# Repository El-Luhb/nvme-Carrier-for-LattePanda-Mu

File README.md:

# nvme Carrier for LattePanda Mu

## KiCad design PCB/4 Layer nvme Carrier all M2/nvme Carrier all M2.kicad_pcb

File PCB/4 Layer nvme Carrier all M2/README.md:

# nvme Carrier for LattePanda Mu

## Specification

### Power Input

- DC 5.5x2.5mm: 12V (Max 10A)
- USB-C 15V

### Internal Interfaces

- 1x M.2 M Key 2242 & 2280 (PCIe 3.0 x1) on the frontside
- 1x M.2 E Key 2242 (PCIe 3.0 x1) on the frontside
- 6x M.2 M Key up to 2280 (PCIe 3.0 x1) on the backside
- RTC battery socket (CR1220 3V)
- CPU fan socket
- 2x CASE fan socket (1x only when using 12V)
- 3x USB 2.0 (1x USB Port)
- MOLEX Connector for 5V (2A) and 12V Supply to HDDs (only when using 12V)

### External Interfaces

- 1x USB 3.2 10Gbps
- 2x USB 2.0
- HDMI 2.0

### Dimension

ITX, 170mm×170mm

### Extras

Carrier BIOS

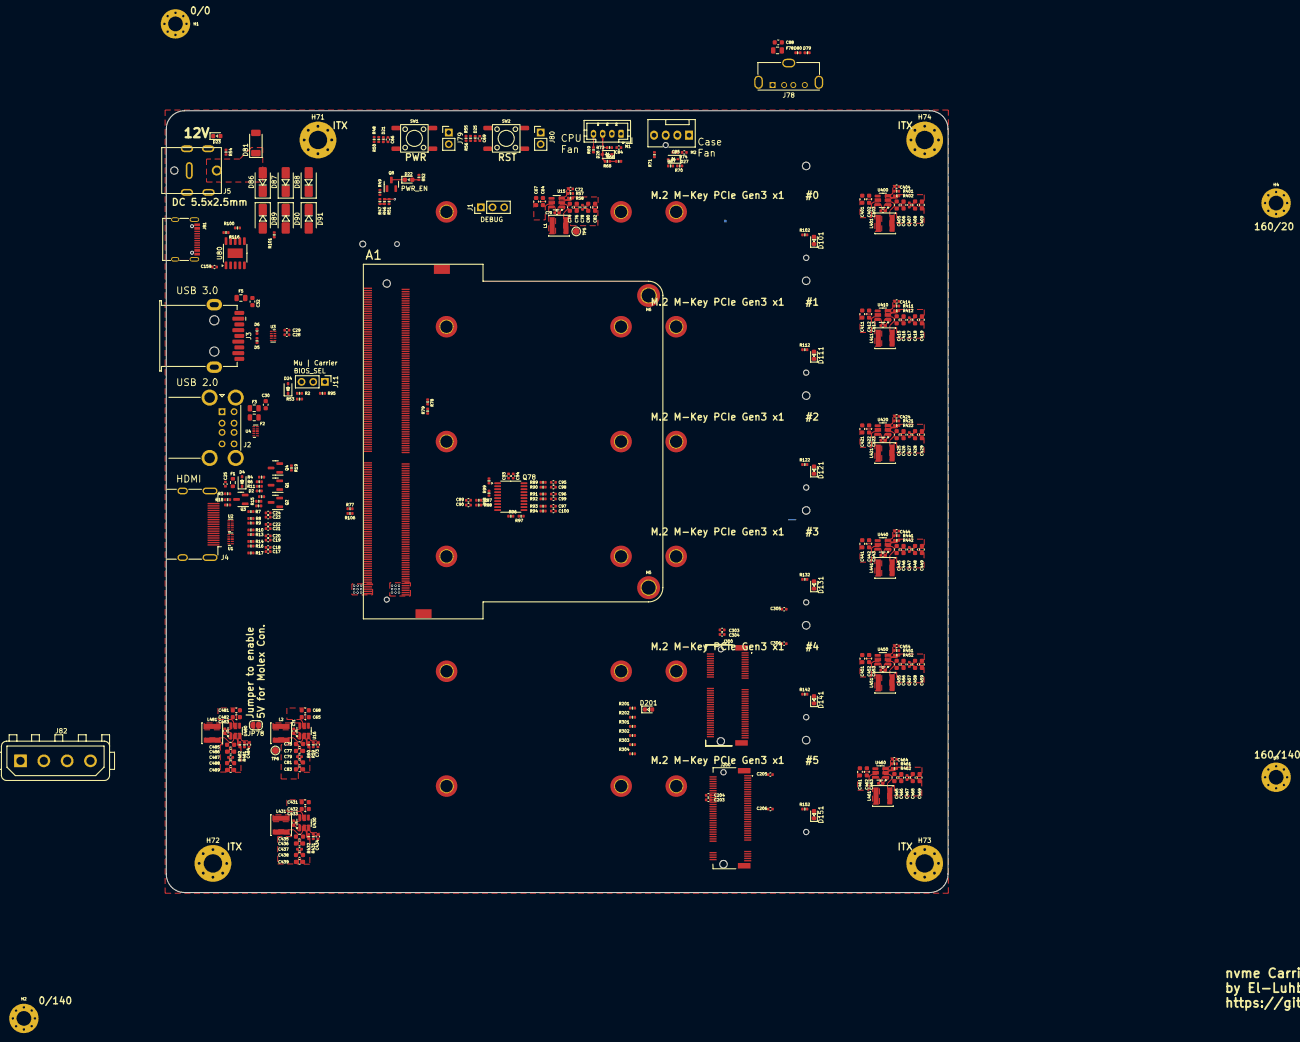
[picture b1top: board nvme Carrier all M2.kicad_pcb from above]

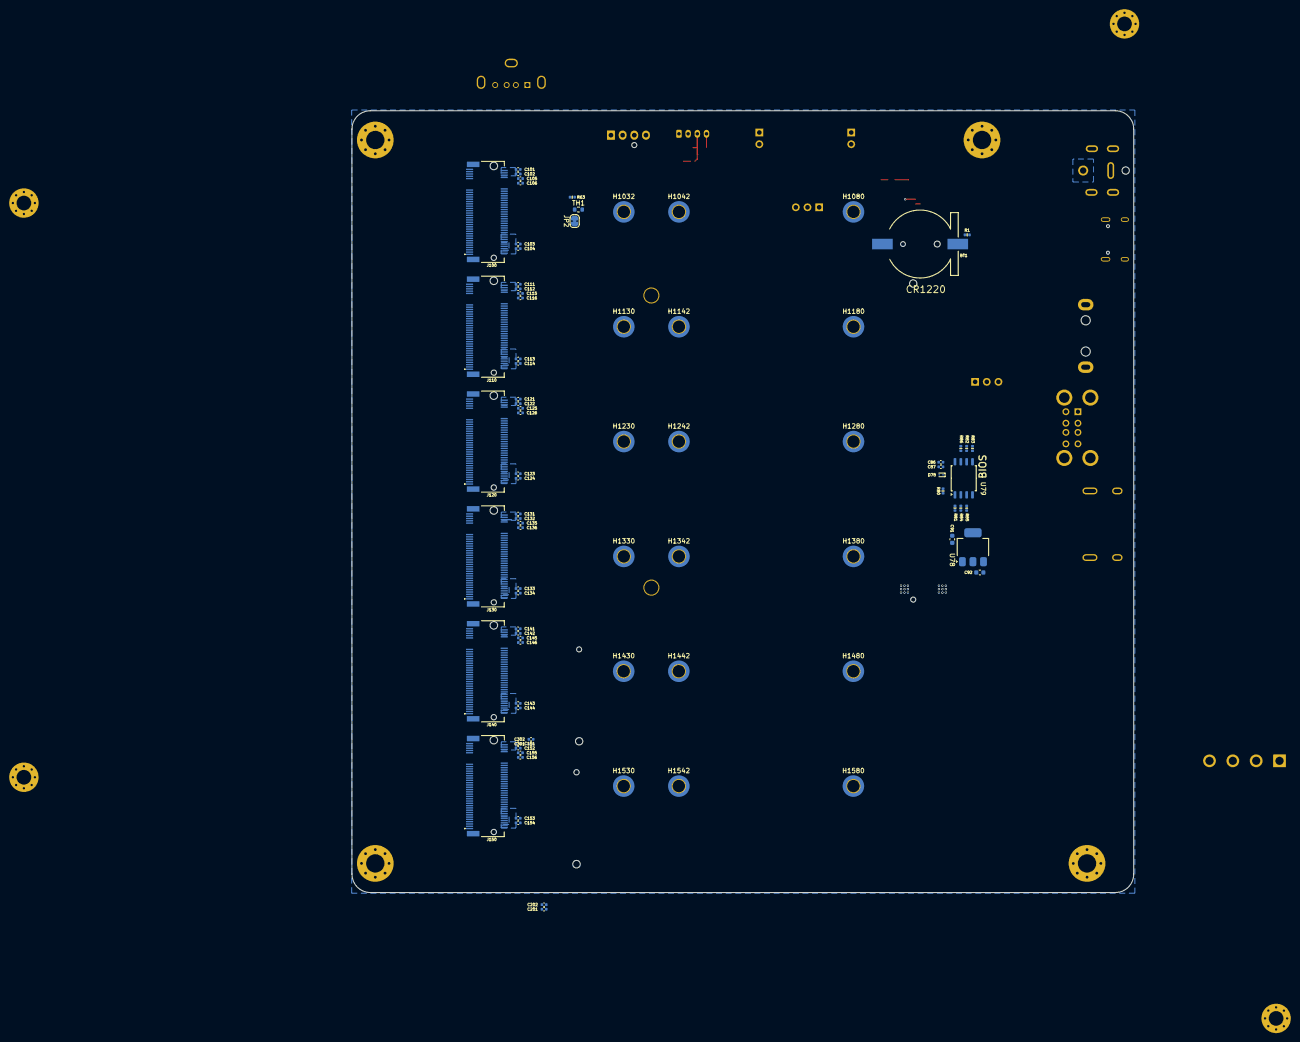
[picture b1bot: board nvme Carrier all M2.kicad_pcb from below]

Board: 4 copper layers, 170.2 x 170.2 mm, 394 parts (83 on the bottom side), 250 nets.

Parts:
A1: LattePanda_Mu; LattePanda_Module_H8.0mm_Horizontal
BT1: Battery_Cell; Battery_Holder_CR1220_S8411-45R
C17, C18, C19, C20, C21, C22, C23, C24, C25, C28, C29, C70, C71, C78, C79, C84, C85, C102, C104, C112, C114, C122, C124, C132, C134, C142, C144, C152, C154, C204, C206, C304, C306, C403, C407, C413, C417, C423, C427, C433, C437, C443, C447, C453, C457, C463, C467, C483, C487: 100nF/50V; C_0402_1005Metric
C30, C32, C74, C75, C76, C77, C80, C81, C82, C83, C88, C91, C405, C406, C408, C409, C415, C416, C418, C419, C425, C426, C428, C429, C435, C436, C438, C439, C445, C446, C448, C449, C455, C456, C458, C459, C465, C466, C468, C469, C485, C486, C488, C489: 22uF/10V; C_0603_1608Metric
C64, C65, C67, C68, C92, C401, C402, C411, C412, C421, C422, C431, C432, C441, C442, C451, C452, C461, C462, C481, C482: 22uF/16V; C_0603_1608Metric
C66, C69, C159: 1uF/16V; C_0402_1005Metric
C72, C73, C404, C414, C424, C434, C444, C454, C464, C484: 12pF/50V; C_0402_1005Metric
C86, C93: 22uF/6.3V; C_0402_1005Metric
C87, C89, C90, C94, C95, C96, C97, C98, C99, C100: 0.1uF/16V; C_0402_1005Metric
C101, C103, C111, C113, C121, C123, C131, C133, C141, C143, C151, C153, C203, C205, C303, C305: 10uF/10V; C_0402_1005Metric
C105, C106, C115, C116, C125, C126, C135, C136, C145, C146, C155, C156, C201, C202, C301, C302: 220nF/50V; C_0402_1005Metric
D1, D2, D3, D5, D6, D21, D25, D79, D80: ESD5V0B03; D_0402_1005Metric
D4, D26, D27: 1N5819WS; D_SOD-323
D22, D23, D101, D111, D121, D131, D141, D151, D201: LED_G; LED_0603_1608Metric
D24: 3V3 Izt=5mA; D_SOD-323
D78: D_Schottky; D_SOD-923
D81: PTVS12VP1UP; D_SOD-128
D86, D87, D88, D89, D90, D91: SS54; D_SMA
F1: 6V/50mA; R_0603_1608Metric
F2, F3, F78: 6V/1A; Fuse_0805_2012Metric
F5: 6V/2A; Fuse_0805_2012Metric
H1, H2, H3, H4: MountingHole_Pad; MountingHole_3.2mm_M3_Pad_Via
H5, H6: MountingHole_Pad; MountingHole_3mm_M2_Pad_TopOnly
H71, H72, H73, H74: MountingHole_Pad; MountingHole_4mm_Pad_Via
H1032, H1042, H1080, H1130, H1142, H1180, H1230, H1242, H1280, H1330, H1342, H1380, H1430, H1442, H1480, H1530, H1542, H1580: MountingHole_M2.5; MountingHole_2.7mm_M2.5_DIN965_Pad_TopBottom
J1, J11: Conn_01x03_Pin; PinHeader_1x03_P2.54mm_Vertical
J2: USB_A_Stacked; USB_A_CUI_UJ2-ADH-TH_Horizontal_Stacked
J3: USB3_A; USB3_A_Receptacle_Wuerth_692122030100
J4: HDMI_A; HDMI_A_Molex_208658-1001_Horizontal
J5: Barrel_Jack_Switch; DC_Jack_DC007B_30V_10A
J78: USB_A; USB_A_Molex_105057_Vertical
J79, J80: Conn_01x02_Pin; PinHeader_1x02_P2.54mm_Vertical
J81: USB_C_Receptacle_USB2.0_14P; USB_C_Receptacle_G-Switch_GT-USB-7010ASV
J82: Conn_01x04; TE_MATE-N-LOK_350211-1_1x04_P5.08mm_Vertical
J100, J110, J120, J130, J140, J150, J200: Bus_M.2_Socket_M; PCIe_M.2_Connectors_P=0.5mm_H=4.2mm_KeyM
J300: Bus_M.2_Socket_E; PCIe_M.2_Connectors_P=0.5mm_H=4.2mm_KeyE
JP2: NTC_Test; SolderJumper-2_P1.3mm_Bridged_RoundedPad1.0x1.5mm
JP78: SolderJumper_2_Open; SolderJumper-2_P1.3mm_Open_RoundedPad1.0x1.5mm
L1, L2, L401, L411, L421, L431, L441, L451, L461, L481: 2.2uH/4.3A; L_Sunlord_SWPA4020S
M1: Fan_4pin; JST_PH_B4B-PH-K_1x04_P2.00mm_Vertical
M2: Fan_4pin; FanPinHeader_1x04_P2.54mm_Vertical
Q1, Q8: 2N7002; SOT-23
Q2, Q3, Q4: 2SK3018; SOT-23
Q78: 9DBL411BGLFT; TSSOP-20_4.4x6.5mm_P0.65mm
R1, R11, R47, R101: 1K/1%; R_0402_1005Metric
R2, R49, R50, R56, R58, R63, R95, R100, R303, R304, R482: 10K/1%; R_0402_1005Metric
R3, R5, R15, R18, R19, R52, R53, R102, R112, R122, R132, R142, R152, R201: 2.2K/1%; R_0402_1005Metric
R4: 1M/1%; R_0402_1005Metric
R6, R54, R66, R67, R68, R70: 21.5K/1%; R_0402_1005Metric
R7, R8, R9, R10, R13, R14, R16, R17: 470R/1%; R_0402_1005Metric
R46, R48, R55, R69, R71: 100R/1%; R_0402_1005Metric
R51, R59, R77, R78, R79, R96, R97, R98, R99, R106, R401, R411, R421, R431, R441, R451, R461: 100K/1%; R_0402_1005Metric
R57, R481: 75K/1%; R_0402_1005Metric
R60, R402, R412, R422, R432, R442, R452, R462: 22K/1%; R_0402_1005Metric
R72, R74: 4.7K/1%; R_0402_1005Metric
R80: 120K/1%; R_0402_1005Metric
R81: 0R; R_0402_1005Metric
R82, R83, R84, R85, R86: 15R/1%; R_0402_1005Metric
R87, R88, R89, R90, R91, R92, R93, R94: 33R/5%; R_0402_1005Metric
R116: 56K/1%; R_0402_1005Metric
R202, R301, R302: 0R/1%; R_0402_1005Metric
SW1, SW2: SW_Push; SW_Push_6x6x6
TH1: NTC-10K; R_0603_1608Metric
TP5, TP6: TestPoint; TestPoint_Pad_D1.5mm
U1, U2: TPAZ1023-04F; Diodes_UDFN-10_1.0x2.5mm_P0.5mm
U3, U4: ULC0524P; Diodes_UDFN-10_1.0x2.5mm_P0.5mm
U15, U16, U400, U410, U420, U430, U440, U450, U460, U480: SY8253ADC; TSOT-23-6
U78: AMS1117-3.3; SOT-223-3_TabPin2
U79: W25Q128JVSIQ; SOIC-8_5.23x5.23mm_P1.27mm
U80: CH224K; SSOP-10-1EP_3.9x4.9mm_P1mm_EP2.1x3.3mm

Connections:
5V_HDMI_VCC: C25.1, D4.1 (K), F1.1, R15.1, R18.1
+3V3: C73.1, C75.2, C77.2, C79.1, C81.2, C83.2, C93.1, C94.1, C203.2, C204.2, C205.2, C206.2, C303.2, C304.2, C305.2, C306.2, J200.2 (3.3V), J200.4 (3.3V), J200.12 (3.3V), J200.14 (3.3V), J200.16 (3.3V), J200.18 (3.3V), J200.70 (3.3V), J200.72 (3.3V), J200.74 (3.3V), J300.2 (3.3V), J300.4 (3.3V), J300.72 (3.3V), J300.74 (3.3V), L2.2, Q1.1 (G), Q2.1 (G), Q3.1 (G), Q78.4 (VDDA), Q78.9 (VDD_IO), Q78.18 (VDD_IO), R3.1, R4.1, R5.1, R50.2, R52.2, R56.2, R59.2, R63.1, R201.2, R303.2, R304.1, TP6.1
+3V3 Bios: C91.2, D78.2 (A), U78.2 (VO)
+3V3a: C101.2, C102.2, C103.2, C104.2, C404.1, C405.2, C406.2, C407.1, C408.2, C409.2, J100.2 (3.3V), J100.4 (3.3V), J100.12 (3.3V), J100.14 (3.3V), J100.16 (3.3V), J100.18 (3.3V), J100.70 (3.3V), J100.72 (3.3V), J100.74 (3.3V), L401.2, R102.2, R401.2
+3V3b: C111.2, C112.2, C113.2, C114.2, C414.1, C415.2, C416.2, C417.1, C418.2, C419.2, J110.2 (3.3V), J110.4 (3.3V), J110.12 (3.3V), J110.14 (3.3V), J110.16 (3.3V), J110.18 (3.3V), J110.70 (3.3V), J110.72 (3.3V), J110.74 (3.3V), L411.2, R112.2, R411.2
+3V3c: C121.2, C122.2, C123.2, C124.2, C424.1, C425.2, C426.2, C427.1, C428.2, C429.2, J120.2 (3.3V), J120.4 (3.3V), J120.12 (3.3V), J120.14 (3.3V), J120.16 (3.3V), J120.18 (3.3V), J120.70 (3.3V), J120.72 (3.3V), J120.74 (3.3V), L421.2, R122.2, R421.2
+3V3d: C131.2, C132.2, C133.2, C134.2, C444.1, C445.2, C446.2, C447.1, C448.2, C449.2, J130.2 (3.3V), J130.4 (3.3V), J130.12 (3.3V), J130.14 (3.3V), J130.16 (3.3V), J130.18 (3.3V), J130.70 (3.3V), J130.72 (3.3V), J130.74 (3.3V), L441.2, R132.2, R441.2
+3V3e: C141.2, C142.2, C143.2, C144.2, C454.1, C455.2, C456.2, C457.1, C458.2, C459.2, J140.2 (3.3V), J140.4 (3.3V), J140.12 (3.3V), J140.14 (3.3V), J140.16 (3.3V), J140.18 (3.3V), J140.70 (3.3V), J140.72 (3.3V), J140.74 (3.3V), L451.2, R142.2, R451.2
+3V3f: C151.2, C152.2, C153.2, C154.2, C464.1, C465.2, C466.2, C467.1, C468.2, C469.2, J150.2 (3.3V), J150.4 (3.3V), J150.12 (3.3V), J150.14 (3.3V), J150.16 (3.3V), J150.18 (3.3V), J150.70 (3.3V), J150.72 (3.3V), J150.74 (3.3V), L461.2, R152.2, R461.2
+3V3g: C434.1, C435.2, C436.2, C437.1, C438.2, C439.2, L431.2, R431.2
+5V: C30.2, C32.2, C72.1, C74.2, C76.2, C78.1, C80.2, C82.2, C84.1, C88.2, D4.2 (A), D26.1 (K), F2.1, F3.1, F5.1, F78.1, L1.2, M1.2 (+), R57.2, R72.1, TP5.1
+5Va: C484.1, C485.2, C486.2, C487.1, C488.2, C489.2, J82.4, L481.2, R481.2
+12V: A1.250 (VIN), A1.251 (VIN), A1.252 (VIN), A1.253 (VIN), A1.254 (VIN), A1.255 (VIN), A1.256 (VIN), A1.257 (VIN), A1.258 (VIN), A1.259 (VIN), A1.260 (VIN), C85.1, D27.1 (K), D81.1 (K), D86.2 (A), D87.2 (A), D88.2 (A), J5.1, J82.1, M2.2 (+), R74.1
+15V: D89.2 (A), D90.2 (A), D91.2 (A), J81.A4 (VBUS), J81.A9 (VBUS), J81.B4 (VBUS), J81.B9 (VBUS), R100.2, R101.2
+BATT: A1.115 (VBAT), R1.1
/BIOS/SPI-CS: A1.165 (~SPI_CS), R81.1
/BIOS/SPI-IO0: A1.159 (SPI_MOSI/SPI_IO0), R83.1
/BIOS/SPI-IO1: A1.163 (SPI_MISO/SPI_IO1), R84.1
/BIOS/SPI-IO2: A1.161 (SPI_IO2), R85.1
/BIOS/SPI-IO3: A1.153 (SPI_IO3), R86.1
/BIOS/SPI_CLK: A1.155 (SPI_CLK), R82.1
/Fan_Temp/FAN_1_PWM: A1.2 (FAN1_PWM), R69.1
/Fan_Temp/FAN_1_TAC: A1.4 (FAN1_TAC), R66.1, R68.2
/Fan_Temp/FAN_2_PWM: A1.6 (FAN2_PWM), R71.1
/Fan_Temp/FAN_2_TAC: A1.8 (FAN2_TAC), R67.1, R70.1
/Fan_Temp/TEMP: A1.9 (TSENSE), JP2.1 (A)
/HDMI DP/DDC_SCL: D1.2 (A2), J4.15 (SCL), Q2.3 (D), R15.2
/HDMI DP/DDC_SDA: D3.2 (A2), J4.16 (SDA), Q3.3 (D), R18.2
/HDMI DP/DDI_B_DDC_SCL: A1.171 (DDIB_DDC_SCL), Q2.2 (S), R5.2
/HDMI DP/DDI_B_DDC_SDA: A1.169 (DDIB_DDC_SDA), Q3.2 (S), R3.2
/HDMI DP/DDI_B_HPD: A1.183 (DDIB_HPD), Q1.2 (S), R4.2
/HDMI DP/DDI_B_TX0+: A1.217 (DDIB_TX0+), C17.1
/HDMI DP/DDI_B_TX0-: A1.215 (DDIB_TX0-), C18.1
/HDMI DP/DDI_B_TX1+: A1.211 (DDIB_TX1+), C19.1
/HDMI DP/DDI_B_TX1-: A1.209 (DDIB_TX1-), C20.1
/HDMI DP/DDI_B_TX2+: A1.205 (DDIB_TX2+), C21.1
/HDMI DP/DDI_B_TX2-: A1.203 (DDIB_TX2-), C22.1
/HDMI DP/DDI_B_TX3+: A1.199 (DDIB_TX3+), C23.1
/HDMI DP/DDI_B_TX3-: A1.197 (DDIB_TX3-), C24.1
/HDMI DP/HPD: D2.2 (A2), J4.19 (HPD), R11.2
/HDMI DP/TCP_0_HPD: A1.187 (TCP0_HPD), R106.1
/HDMI DP/TMDS_CK+: C23.2, J4.10 (CK+), R8.1, U2.4, U2.7 (NC)
/HDMI DP/TMDS_CK-: C24.2, J4.12 (CK-), R7.1, U2.5, U2.6 (NC)
/HDMI DP/TMDS_D0+: C21.2, J4.7 (D0+), R10.1, U2.1, U2.10 (NC)
/HDMI DP/TMDS_D0-: C22.2, J4.9 (D0-), R9.1, U2.2, U2.9 (NC)
/HDMI DP/TMDS_D1+: C19.2, J4.4 (D1+), R14.1, U1.4, U1.7 (NC)
/HDMI DP/TMDS_D1-: C20.2, J4.6 (D1-), R13.1, U1.5, U1.6 (NC)
/HDMI DP/TMDS_D2+: C17.2, J4.1 (D2+), R17.1, U1.1, U1.10 (NC)
/HDMI DP/TMDS_D2-: C18.2, J4.3 (D2-), R16.1, U1.2, U1.9 (NC)
/LattePanda Module/CLKREQ3: A1.100 (~CLKREQ3), J100.52 (~CLKREQ), R79.1
/LattePanda Module/CLKREQ4: A1.102 (~CLKREQ4), J110.52 (~CLKREQ), R78.1
/LattePanda Module/HSIO_0_TX+: A1.13 (HSIO0_TX+), C29.1
/LattePanda Module/HSIO_0_TX-: A1.15 (HSIO0_TX-), C28.1
/LattePanda Module/HSIO_1_RX+: A1.22 (HSIO1_RX+), J100.43 (PERp0/SATA-B-)
/LattePanda Module/HSIO_1_RX-: A1.24 (HSIO1_RX-), J100.41 (PERn0/SATA-B+)
/LattePanda Module/HSIO_1_TX+: A1.19 (HSIO1_TX+), C105.1
/LattePanda Module/HSIO_1_TX-: A1.21 (HSIO1_TX-), C106.1
/LattePanda Module/HSIO_2_RX+: A1.28 (HSIO2_RX+), J110.43 (PERp0/SATA-B-)
/LattePanda Module/HSIO_2_RX-: A1.30 (HSIO2_RX-), J110.41 (PERn0/SATA-B+)
/LattePanda Module/HSIO_2_TX+: A1.25 (HSIO2_TX+), C115.1
/LattePanda Module/HSIO_2_TX-: A1.27 (HSIO2_TX-), C116.1
/LattePanda Module/HSIO_3_RX+: A1.34 (HSIO3_RX+), J120.43 (PERp0/SATA-B-)
/LattePanda Module/HSIO_3_RX-: A1.36 (HSIO3_RX-), J120.41 (PERn0/SATA-B+)
/LattePanda Module/HSIO_3_TX+: A1.31 (HSIO3_TX+), C125.1
/LattePanda Module/HSIO_3_TX-: A1.33 (HSIO3_TX-), C126.1
/LattePanda Module/HSIO_6_RX+: A1.64 (HSIO6_RX+), J200.43 (PERp0/SATA-B-)
/LattePanda Module/HSIO_6_RX-: A1.66 (HSIO6_RX-), J200.41 (PERn0/SATA-B+)
/LattePanda Module/HSIO_6_TX+: A1.61 (HSIO6_TX+), C201.1
/LattePanda Module/HSIO_6_TX-: A1.63 (HSIO6_TX-), C202.1
/LattePanda Module/HSIO_8_RX+: A1.40 (HSIO8_RX+), J130.43 (PERp0/SATA-B-)
/LattePanda Module/HSIO_8_RX-: A1.42 (HSIO8_RX-), J130.41 (PERn0/SATA-B+)
/LattePanda Module/HSIO_8_TX+: A1.37 (HSIO8_TX+), C135.1
/LattePanda Module/HSIO_8_TX-: A1.39 (HSIO8_TX-), C136.1
/LattePanda Module/HSIO_9_RX+: A1.46 (HSIO9_RX+), J140.43 (PERp0/SATA-B-)
/LattePanda Module/HSIO_9_RX-: A1.48 (HSIO9_RX-), J140.41 (PERn0/SATA-B+)
/LattePanda Module/HSIO_9_TX+: A1.43 (HSIO9_TX+), C145.1
/LattePanda Module/HSIO_9_TX-: A1.45 (HSIO9_TX-), C146.1
/LattePanda Module/HSIO_10_RX+: A1.52 (HSIO10_RX+), J150.43 (PERp0/SATA-B-)
/LattePanda Module/HSIO_10_RX-: A1.54 (HSIO10_RX-), J150.41 (PERn0/SATA-B+)
/LattePanda Module/HSIO_10_TX+: A1.49 (HSIO10_TX+), C155.1
/LattePanda Module/HSIO_10_TX-: A1.51 (HSIO10_TX-), C156.1
/LattePanda Module/HSIO_11_RX+: A1.58 (HSIO11_RX+), J300.41 (PERp0)
/LattePanda Module/HSIO_11_RX-: A1.60 (HSIO11_RX-), J300.43 (PERn0)
/LattePanda Module/HSIO_11_TX+: A1.55 (HSIO11_TX+), C301.1
/LattePanda Module/HSIO_11_TX-: A1.57 (HSIO11_TX-), C302.1
/LattePanda Module/REFCLK0+: A1.85 (REFCLK0+), J200.55 (REFCLKp)
/LattePanda Module/REFCLK0-: A1.87 (REFCLK0-), J200.53 (REFCLKn)
/LattePanda Module/REFCLK1+: A1.91 (REFCLK1+), J300.47 (REFCLKp0)
/LattePanda Module/REFCLK1-: A1.93 (REFCLK1-), J300.49 (REFCLKn0)
/LattePanda Module/REFCLK2+: A1.97 (REFCLK2+), Q78.2 (DIF_IN-)
/LattePanda Module/REFCLK2-: A1.99 (REFCLK2-), Q78.3 (DIF_IN+)
/LattePanda Module/REFCLK3+: A1.88 (REFCLK3+), J100.55 (REFCLKp)
/LattePanda Module/REFCLK3-: A1.90 (REFCLK3-), J100.53 (REFCLKn)
/LattePanda Module/REFCLK4+: A1.94 (REFCLK4+), J110.55 (REFCLKp)
/LattePanda Module/REFCLK4-: A1.96 (REFCLK4-), J110.53 (REFCLKn)
/LattePanda Module/USB_2_P4+: A1.70 (USB2_P4+), D79.2 (A2), J78.3 (D+)
/LattePanda Module/USB_2_P4-: A1.72 (USB2_P4-), D80.2 (A2), J78.2 (D-)
/LattePanda Module/~PWR_SW: A1.1 (~PWRBTN), R48.2
/LattePanda Module/~RST_SW: A1.3 (~RSTBTN), R55.2
/M.2 E&M-Key/PCIE30_TX0_N: C202.2, J200.47 (PETn0/SATA-A-)
/M.2 E&M-Key/PCIE30_TX0_P: C201.2, J200.49 (PETp0/SATA-A+)
/M.2 E&M-Key/PCIE30_TX1_N: C302.2, J300.37 (PETn0)
/M.2 E&M-Key/PCIE30_TX1_P: C301.2, J300.35 (PETp0)
/M.2 E&M-Key/~CLKREQE: J300.53 (~CLKREQ0), R302.1
/M.2 E&M-Key/~CLKREQM: J200.52 (~CLKREQ), R202.1
/M.2 M Key/CLKREQM2: J120.52 (~CLKREQ), Q78.1 (OE0#), R99.1
/M.2 M Key/CLKREQM3: J130.52 (~CLKREQ), Q78.16 (OE1#), R97.1
/M.2 M Key/CLKREQM4: J140.52 (~CLKREQ), Q78.13 (OE2#), R96.1
/M.2 M Key/CLKREQM5: J150.52 (~CLKREQ), Q78.6 (OE3#), R98.1
/M.2 M Key/CON_PCIE_TX_0+: C105.2, J100.49 (PETp0/SATA-A+)
/M.2 M Key/CON_PCIE_TX_0-: C106.2, J100.47 (PETn0/SATA-A-)
/M.2 M Key/CON_PCIE_TX_1+: C115.2, J110.49 (PETp0/SATA-A+)
/M.2 M Key/CON_PCIE_TX_1-: C116.2, J110.47 (PETn0/SATA-A-)
/M.2 M Key/CON_PCIE_TX_2+: C125.2, J120.49 (PETp0/SATA-A+)
/M.2 M Key/CON_PCIE_TX_2-: C126.2, J120.47 (PETn0/SATA-A-)
/M.2 M Key/CON_PCIE_TX_3+: C135.2, J130.49 (PETp0/SATA-A+)
/M.2 M Key/CON_PCIE_TX_3-: C136.2, J130.47 (PETn0/SATA-A-)
/M.2 M Key/CON_PCIE_TX_4+: C145.2, J140.49 (PETp0/SATA-A+)
/M.2 M Key/CON_PCIE_TX_4-: C146.2, J140.47 (PETn0/SATA-A-)
/M.2 M Key/CON_PCIE_TX_5+: C155.2, J150.49 (PETp0/SATA-A+)
/M.2 M Key/CON_PCIE_TX_5-: C156.2, J150.47 (PETn0/SATA-A-)
/M.2 M Key/REFCLKM2+: C98.2, J120.55 (REFCLKp)
/M.2 M Key/REFCLKM2-: C95.2, J120.53 (REFCLKn)
/M.2 M Key/REFCLKM3+: C99.2, J130.55 (REFCLKp)
/M.2 M Key/REFCLKM3-: C96.2, J130.53 (REFCLKn)
/M.2 M Key/REFCLKM4+: C100.2, J140.55 (REFCLKp)
/M.2 M Key/REFCLKM4-: C97.2, J140.53 (REFCLKn)
/M.2 M Key/REFCLKM5+: C90.1, J150.55 (REFCLKp)
/M.2 M Key/REFCLKM5-: C89.1, J150.53 (REFCLKn)
/PCIe CLK Buffer/DIF0+: Q78.19 (DIF0+), R90.2
/PCIe CLK Buffer/DIF0-: Q78.20 (DIF0-), R89.1
/PCIe CLK Buffer/DIF1+: Q78.14 (DIF1+), R92.2
/PCIe CLK Buffer/DIF1-: Q78.15 (DIF1-), R91.1
/PCIe CLK Buffer/DIF2+: Q78.11 (DIF2+), R94.2
/PCIe CLK Buffer/DIF2-: Q78.12 (DIF2-), R93.1
/PCIe CLK Buffer/DIF3+: Q78.8 (DIF3+), R88.1
/PCIe CLK Buffer/DIF3-: Q78.7 (DIF3-), R87.2
/PCIe CLK Buffer/RDIF0+: C98.1, R90.1
/PCIe CLK Buffer/RDIF0-: C95.1, R89.2
/PCIe CLK Buffer/RDIF1+: C99.1, R92.1
/PCIe CLK Buffer/RDIF1-: C96.1, R91.2
/PCIe CLK Buffer/RDIF2+: C100.1, R94.1
/PCIe CLK Buffer/RDIF2-: C97.1, R93.2
/PCIe CLK Buffer/RDIF3+: C90.2, R88.2
/PCIe CLK Buffer/RDIF3-: C89.2, R87.1
/PSU/PWR_EN: JP78.1 (A), R46.2, R51.2, U15.4 (EN), U16.4 (EN), U400.4 (EN), U410.4 (EN), U420.4 (EN), U430.4 (EN), U440.4 (EN), U450.4 (EN), U460.4 (EN)
/USB/CON_USB1_D_N: A1.79 (USB2_P3-), J2.2 (D1-), U4.2, U4.9 (NC)
/USB/CON_USB1_D_P: A1.81 (USB2_P3+), J2.3 (D1+), U4.1, U4.10 (NC)
/USB/CON_USB2_D_N: A1.73 (USB2_P2-), J2.6 (D2-), U4.5, U4.6 (NC)
/USB/CON_USB2_D_P: A1.75 (USB2_P2+), J2.7 (D2+), U4.4, U4.7 (NC)
/USB/CON_USB3_D_N: A1.67 (USB2_P1-), D6.2 (A2), J3.2 (D-)
/USB/CON_USB3_D_P: A1.69 (USB2_P1+), D5.2 (A2), J3.3 (D+)
/USB/CON_USB3_SSRX_N: A1.18 (HSIO0_RX-), J3.5 (SSRX-), U3.5, U3.6 (NC)
/USB/CON_USB3_SSRX_P: A1.16 (HSIO0_RX+), J3.6 (SSRX+), U3.4, U3.7 (NC)
/USB/CON_USB3_SSTX_N: C28.2, J3.8 (SSTX-), U3.2, U3.9 (NC)
/USB/CON_USB3_SSTX_P: C29.2, J3.9 (SSTX+), U3.1, U3.10 (NC)
/~PLT_RST: A1.105 (~PLTRST), J100.50 (~PERST), J110.50 (~PERST), J120.50 (~PERST), J130.50 (~PERST), J140.50 (~PERST), J150.50 (~PERST), J200.50 (~PERST), J300.52 (~PERST0)
/~PWR_LED/~PSON: A1.5 (SLS_S0), R19.1, R46.1, R47.1
/~WAKE: A1.103 (~WAKE), J100.54 (~PEWAKE), J110.54 (~PEWAKE), J120.54 (~PEWAKE), J130.54 (~PEWAKE), J140.54 (~PEWAKE), J150.54 (~PEWAKE), J200.54 (~PEWAKE), J300.55 (~PEWAKE0)
GND: A1.11 (GND), A1.14 (GND), A1.17 (GND), A1.20 (GND), A1.23 (GND), A1.26 (GND), A1.29 (GND), A1.32 (GND), A1.35 (GND), A1.38 (GND), A1.41 (GND), A1.44 (GND), A1.47 (GND), A1.50 (GND), A1.53 (GND), A1.56 (GND), A1.59 (GND), A1.62 (GND), A1.65 (GND), A1.68 (GND), A1.71 (GND), A1.74 (GND), A1.77 (GND), A1.80 (GND), A1.83 (GND), A1.86 (GND), A1.89 (GND), A1.92 (GND), A1.95 (GND), A1.98 (GND), A1.101 (GND), A1.107 (GND), A1.110 (GND), A1.113 (GND), A1.116 (GND), A1.135 (GND), A1.136 (GND), A1.151 (GND), A1.158 (GND), A1.167 (GND), A1.170 (GND), A1.181 (GND), A1.182 (GND), A1.188 (GND), A1.189 (GND), A1.194 (GND), A1.195 (GND), A1.200 (GND), A1.201 (GND), A1.206 (GND), A1.207 (GND), A1.212 (GND), A1.213 (GND), A1.218 (GND), A1.219 (GND), A1.224 (GND), A1.225 (GND), A1.230 (GND), A1.231 (GND), A1.236 (GND), A1.237 (GND), A1.242 (GND), A1.243 (GND), A1.248 (GND), A1.249 (GND), A1.MP (Mountinge_Pads), BT1.2 (-), C25.2, C30.1, C32.1, C64.1, C65.1, C66.2, C67.1, C68.1, C69.2, C74.1, C75.1, C76.1, C77.1, C78.2, C79.2, C80.1, C81.1, C82.1, C83.1, C84.2, C85.2, C86.2, C87.2, C88.1, C91.1, C92.1, C93.2, C94.2, C101.1, C102.1, C103.1, C104.1, C111.1, C112.1, C113.1, C114.1, C121.1, C122.1, C123.1, C124.1, C131.1, C132.1, C133.1, C134.1, C141.1, C142.1, C143.1, C144.1, C151.1, C152.1, C153.1, C154.1, C159.1, C203.1, C204.1, C205.1, C206.1, C303.1, C304.1, C305.1, C306.1, C401.1, C402.1, C405.1, C406.1, C407.2, C408.1, C409.1, C411.1, C412.1, C415.1, C416.1, C417.2, C418.1, C419.1, C421.1, C422.1, C425.1, C426.1, C427.2, C428.1, C429.1, C431.1, C432.1, C435.1, C436.1, C437.2, C438.1, C439.1, C441.1, C442.1, C445.1, C446.1, C447.2, C448.1, C449.1, C451.1, C452.1, C455.1, C456.1, C457.2, C458.1, C459.1, C461.1, C462.1, C465.1, C466.1, C467.2, C468.1, C469.1, C481.1, C482.1, C485.1, C486.1, C487.2, C488.1, C489.1, D1.1 (A1), D2.1 (A1), D3.1 (A1), D5.1 (A1), D6.1 (A1), D21.1 (A1), D23.1 (K), D24.2 (A), D25.1 (A1), D79.1 (A1), D80.1 (A1), D81.2 (A), H1.1, H2.1, H3.1, H4.1, H5.1, H6.1, H71.1, H72.1, H73.1, H74.1, H1032.1, H1042.1, H1080.1, H1130.1, H1142.1, H1180.1, H1230.1, H1242.1, H1280.1, H1330.1, H1342.1, H1380.1, H1430.1, H1442.1, H1480.1, H1530.1, H1542.1, H1580.1, J1.3, J2.4 (GND1), J2.8 (GND2), J2.9 (Shield), J3.4 (GND), J3.7 (DRAIN), J3.10 (SHIELD), J4.2 (D2S), J4.5 (D1S), J4.8 (D0S), J4.11 (CKS), J4.17 (GND), J4.SH, J5.2, J5.3, J78.4 (GND), J78.5 (Shield), J79.1, J80.1, J81.A1 (GND), J81.A12 (GND), J81.B1 (GND), J81.B12 (GND), J81.S1 (SHIELD), J82.2, J82.3, J100.1 (GND), J100.3 (GND), J100.9 (GND), J100.15 (GND), J100.21 (GND), J100.27 (GND), J100.33 (GND), J100.39 (GND), J100.45 (GND), J100.51 (GND), J100.57 (GND), J100.71 (GND), J100.73 (GND), J100.75 (GND), J100.MP1, J100.MP2, J110.1 (GND), J110.3 (GND), J110.9 (GND), J110.15 (GND), J110.21 (GND), J110.27 (GND), J110.33 (GND), J110.39 (GND), J110.45 (GND), J110.51 (GND), J110.57 (GND), J110.71 (GND), J110.73 (GND), J110.75 (GND), J110.MP1, J110.MP2, J120.1 (GND), J120.3 (GND), J120.9 (GND), J120.15 (GND), J120.21 (GND), J120.27 (GND), J120.33 (GND), J120.39 (GND), J120.45 (GND), J120.51 (GND), J120.57 (GND), J120.71 (GND), J120.73 (GND), J120.75 (GND), J120.MP1, J120.MP2, J130.1 (GND), J130.3 (GND), J130.9 (GND), J130.15 (GND), J130.21 (GND), J130.27 (GND), J130.33 (GND), J130.39 (GND), J130.45 (GND), J130.51 (GND), J130.57 (GND), J130.71 (GND), J130.73 (GND), J130.75 (GND), J130.MP1, J130.MP2, J140.1 (GND), J140.3 (GND), J140.9 (GND), J140.15 (GND), J140.21 (GND), J140.27 (GND), J140.33 (GND), J140.39 (GND), J140.45 (GND), J140.51 (GND), J140.57 (GND), J140.71 (GND), J140.73 (GND), J140.75 (GND), J140.MP1, J140.MP2, J150.1 (GND), J150.3 (GND), J150.9 (GND), J150.15 (GND), J150.21 (GND), J150.27 (GND), J150.33 (GND), J150.39 (GND), J150.45 (GND), J150.51 (GND), J150.57 (GND), J150.71 (GND), J150.73 (GND), J150.75 (GND), J150.MP1, J150.MP2, J200.1 (GND), J200.3 (GND), J200.9 (GND), J200.15 (GND), J200.21 (GND), J200.27 (GND), J200.33 (GND), J200.39 (GND), J200.45 (GND), J200.51 (GND), J200.57 (GND), J200.71 (GND), J200.73 (GND), J200.75 (GND), J200.MP1, J200.MP2, J300.1 (GND), J300.7 (GND), J300.18 (GND), J300.33 (GND), J300.39 (GND), J300.45 (GND), J300.51 (GND), J300.57 (GND), J300.63 (GND), J300.69 (GND), J300.75 (GND), J300.MP1, J300.MP2, M1.1 (-), M2.1 (-), Q4.2 (S), Q8.2 (S), Q78.5 (GNDA), Q78.10 (GND), Q78.17 (GND), R6.2, R49.1, R51.1, R58.1, R60.1, R66.2, R67.2, R77.2, R78.2, R79.2, R95.1, R96.2, R97.2, R98.2, R99.2, R106.2, R116.2, R202.2, R302.2, R402.1, R412.1, R422.1, R432.1, R442.1, R452.1, R462.1, R482.1, SW1.2, SW2.2, TH1.2, U1.3 (VSS), U1.8 (VSS), U2.3 (VSS), U2.8 (VSS), U3.3 (VSS), U3.8 (VSS), U4.3 (VSS), U4.8 (VSS), U15.2 (GND), U16.2 (GND), U78.1 (GND), U79.4 (GND), U80.11 (GND), U400.2 (GND), U410.2 (GND), U420.2 (GND), U430.2 (GND), U440.2 (GND), U450.2 (GND), U460.2 (GND), U480.2 (GND)
unnamed: A1.12 (SIO_UART_RX), J1.2
unnamed: A1.10 (SIO_UART_TX), J1.1
unnamed: A1.185 (TCP1_HPD), R77.1
unnamed: A1.133 (~BIOS_SEL), J11.2
unnamed: BT1.1 (+), R1.2
unnamed: C66.1, D21.2 (A2), J79.2, R48.1, R50.1, SW1.1
unnamed: D22.2 (A), R52.1
unnamed: D22.1 (K), Q8.3 (D)
unnamed: D23.2 (A), R54.2
unnamed: C69.1, D25.2 (A2), J80.2, R55.1, R56.1, SW2.1
unnamed: D26.2 (A), M1.3 (Tacho), R68.1, R72.2
unnamed: D27.2 (A), M2.3 (Tacho), R70.2, R74.2
unnamed: C86.1, C87.1, D78.1 (K), R80.1, U79.8 (VCC)
unnamed: D101.2 (A), R102.1
unnamed: D101.1 (K), J100.10 (DAS/~DSS/~LED1)
unnamed: D111.2 (A), R112.1
unnamed: D111.1 (K), J110.10 (DAS/~DSS/~LED1)
unnamed: D121.2 (A), R122.1
unnamed: D121.1 (K), J120.10 (DAS/~DSS/~LED1)
unnamed: D131.2 (A), R132.1
unnamed: D131.1 (K), J130.10 (DAS/~DSS/~LED1)
unnamed: D141.2 (A), R142.1
unnamed: D141.1 (K), J140.10 (DAS/~DSS/~LED1)
unnamed: D151.2 (A), R152.1
unnamed: D151.1 (K), J150.10 (DAS/~DSS/~LED1)
unnamed: D201.2 (A), R201.1
unnamed: D201.1 (K), J200.10 (DAS/~DSS/~LED1)
unnamed: F2.2, J2.1 (VBUS1)
unnamed: F3.2, J2.5 (VBUS2)
unnamed: F5.2, J3.1 (VBUS)
unnamed: F1.2, J4.18 (+5V)
unnamed: J11.1, R95.2
unnamed: J11.3, R2.1
unnamed: F78.2, J78.1 (VBUS)
unnamed: J81.A5 (CC1), U80.7 (CC1)
unnamed: J81.B5 (CC2), U80.6 (CC2)
unnamed: J300.50 (SUSCLK), R301.1
unnamed: J300.56 (~W_DISABLE1), R303.1
unnamed: J300.54 (~W_DISABLE2), R304.2
unnamed: JP2.2 (B), R63.2, TH1.1
unnamed: JP78.2 (B), U480.4 (EN)
unnamed: M1.4 (PWM), R69.2
unnamed: M2.4 (PWM), R71.2
unnamed: Q1.3 (D), R6.1, R11.1
unnamed: Q4.3 (D), R7.2, R8.2, R9.2, R10.2, R13.2, R14.2, R16.2, R17.2
unnamed: Q4.1 (G), R19.2
unnamed: Q8.1 (G), R47.2, R49.2
unnamed: C70.2, U15.1 (BOOST)
unnamed: C72.2, R57.1, R58.2, U15.3 (FB)
unnamed: C70.1, L1.1, U15.6 (SW)
unnamed: C71.2, U16.1 (BOOST)
unnamed: C73.2, R59.1, R60.2, U16.3 (FB)
unnamed: C71.1, L2.1, U16.6 (SW)
unnamed: R82.2, U79.6 (CLK)
unnamed: R83.2, U79.5 (DI(IO0))
unnamed: R84.2, U79.2 (DO(IO1))
unnamed: R85.2, U79.3 (IO2)
unnamed: R86.2, U79.7 (IO3)
unnamed: R80.2, R81.2, U79.1 (~CS)
unnamed: R116.1, U80.9 (CFG1)
unnamed: J81.A7 (D-), J81.B7 (D-), U80.5 (DM)
unnamed: J81.A6 (D+), J81.B6 (D+), U80.4 (DP)
unnamed: R100.1, U80.8 (VBUS)
unnamed: C159.2, R101.1, U80.1 (VDD)
unnamed: C403.2, U400.1 (BOOST)
unnamed: C404.2, R401.1, R402.2, U400.3 (FB)
unnamed: C403.1, L401.1, U400.6 (SW)
unnamed: C413.2, U410.1 (BOOST)
unnamed: C414.2, R411.1, R412.2, U410.3 (FB)
unnamed: C413.1, L411.1, U410.6 (SW)
unnamed: C423.2, U420.1 (BOOST)
unnamed: C424.2, R421.1, R422.2, U420.3 (FB)
unnamed: C423.1, L421.1, U420.6 (SW)
unnamed: C433.2, U430.1 (BOOST)
unnamed: C434.2, R431.1, R432.2, U430.3 (FB)
unnamed: C433.1, L431.1, U430.6 (SW)
unnamed: C443.2, U440.1 (BOOST)
unnamed: C444.2, R441.1, R442.2, U440.3 (FB)
unnamed: C443.1, L441.1, U440.6 (SW)
unnamed: C453.2, U450.1 (BOOST)
unnamed: C454.2, R451.1, R452.2, U450.3 (FB)
unnamed: C453.1, L451.1, U450.6 (SW)
unnamed: C463.2, U460.1 (BOOST)
unnamed: C464.2, R461.1, R462.2, U460.3 (FB)
unnamed: C463.1, L461.1, U460.6 (SW)
unnamed: C483.2, U480.1 (BOOST)
unnamed: C484.2, R481.1, R482.2, U480.3 (FB)
unnamed: C483.1, L481.1, U480.6 (SW)
VDC: C64.2, C65.2, C67.2, C68.2, C92.2, C401.2, C402.2, C411.2, C412.2, C421.2, C422.2, C431.2, C432.2, C441.2, C442.2, C451.2, C452.2, C461.2, C462.2, C481.2, C482.2, D86.1 (K), D87.1 (K), D88.1 (K), D89.1 (K), D90.1 (K), D91.1 (K), R53.1, R54.1, U15.5 (VIN), U16.5 (VIN), U78.3 (VI), U400.5 (VIN), U410.5 (VIN), U420.5 (VIN), U430.5 (VIN), U440.5 (VIN), U450.5 (VIN), U460.5 (VIN), U480.5 (VIN)
VPullup: D24.1 (K), R2.2, R53.2

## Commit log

2024-06-23 First Upload
2024-06-23 Add README
2024-06-23 Details on pcie
2024-06-23 Moved internal USB
2024-06-23 Moved internal USB-2
2024-06-25 Parts change for BOM
2024-07-13 BOM update and pdf
2024-07-17 Rework for PSU and REFCLK
2024-07-19 change to 12V and more work to do
2024-08-18 Add new Buffer Chip for rework
2024-08-19 Rework started with PCIe
2024-08-21 PCIe and CLK Buffenr Lines
2024-08-21 Work
2024-08-22 change to 4 Layer - 2 Layer later if possible
2024-08-22 Prototyp_1
2024-08-23 wrong Partnumber for the 33R
2024-09-19 Silk and BOM changes
2024-09-19 README edit and new JPGs
2024-09-19 edit gitignore
2024-09-19 add jpg of the Prototype
2024-09-19 USB 3 listed in BOM
2024-10-05 Correction for #8
2024-11-07 Add example Carrier Case
2024-12-30 Update STL files for the Case
2025-01-30 Fix USB3.2. And Updated some C
    Fix USB3.2 Error (twisted Tx and Rx). And Updated some C from 22uF/10V to 22uF/16V
2025-01-30 Fixed Fix for USB3.2
2025-01-31 update the PDF
2025-01-31 new JPG, new 3V3 names and del the M.2 60mm mounts
2025-01-31 LED 3V3x rename
2025-02-01 first all M.2 try
2025-02-06 first all-M.2 version
2025-02-06 Edit README for all-M.2 and add JPG
